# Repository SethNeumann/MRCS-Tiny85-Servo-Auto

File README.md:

# REPO NAME: MRCS-Tiny85-Servo-Auto 

## License: Creative Commons Attribution-NonCommercial-ShareAlike

Tiny85 servo switch machine controller. This version is based on load sensing to determine when the motor has completed it's travel and skipping the pots which can get bumped or drift over time.

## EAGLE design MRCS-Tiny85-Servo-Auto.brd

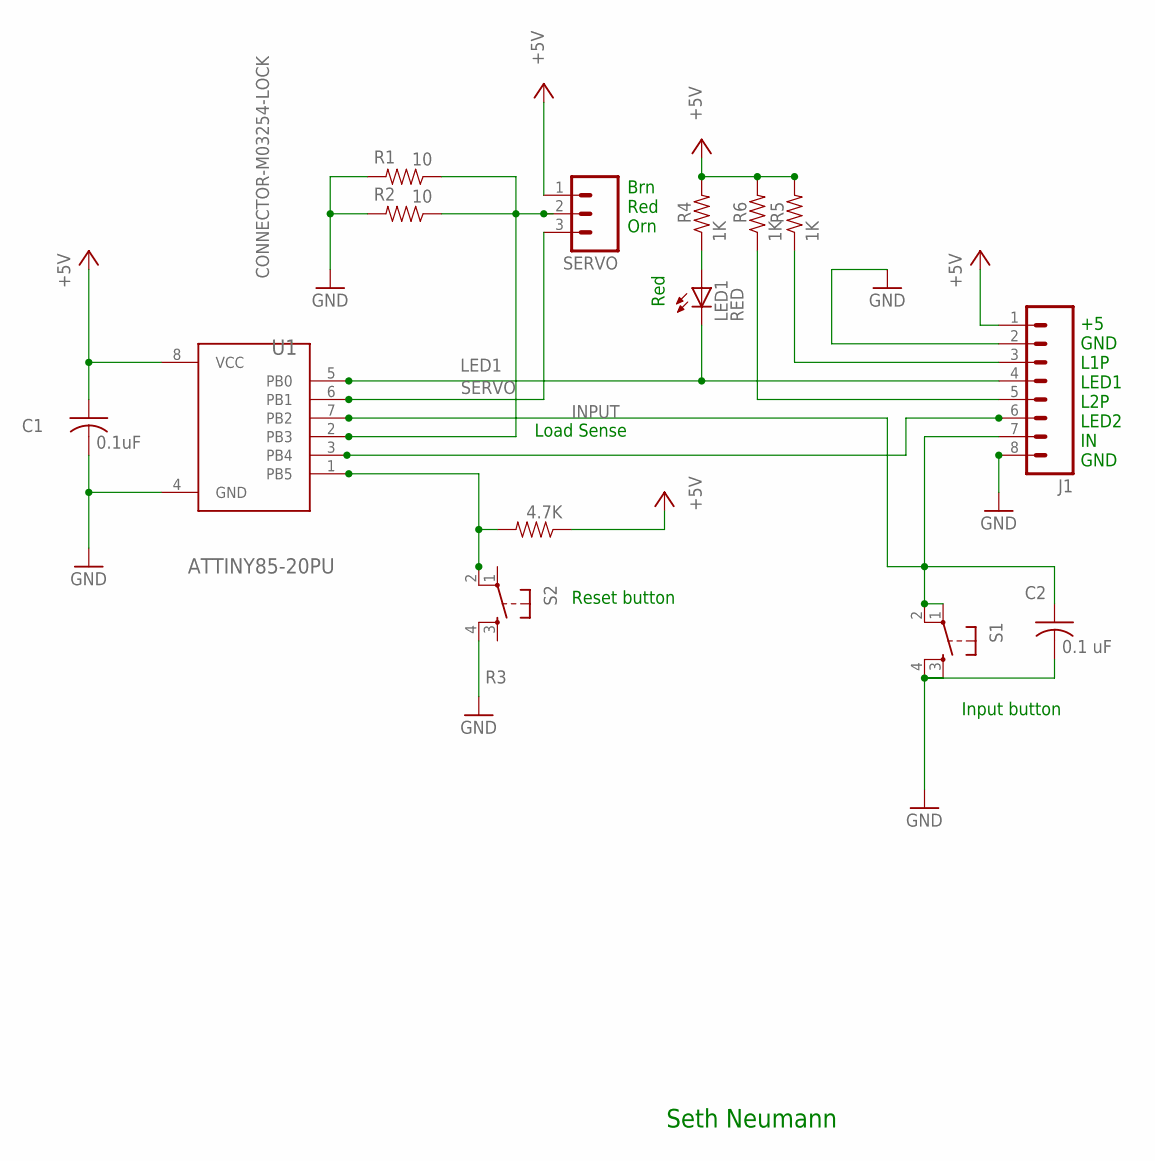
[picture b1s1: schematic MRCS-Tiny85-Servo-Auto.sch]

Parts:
C1: 0.1uF; C-PTH-0.100
C2: 0.1 uF; C-PTH-0.100
J1: CONNECTOR-M08LOCK; 1X08_LOCK
LED1: RED; LED3MM
R1, R2: 10; AXIAL-0.4-RES
R3: 4.7K; AXIAL-0.4-RES
R4, R5, R6: 1K; AXIAL-0.4-RES
S1, S2: TAC_SWITCHPTH; TACTILE-PTH
SERVO: CONNECTOR-M03254-LOCK; 3POL254
U1: ATTINY85-20PU; DIP762W46P254L927H533Q8B

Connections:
+5V: C1.1, J1.1, R3.P$1 (1), R4.P$2 (2), R5.P$2 (2), R6.P$2 (2), SERVO.1, U1.8 (VCC)
ADC3: R1.P$1 (1), R2.P$1 (1), SERVO.2, U1.2 (PB3)
GND: C1.2, C2.2, J1.2, J1.8, R1.P$2 (2), R2.P$2 (2), S1.3, S1.4, S2.4, U1.4 (GND)
INPUT: C2.1, J1.7, S1.1, S1.2, U1.7 (PB2)
LED1: J1.4, LED1.K (C), U1.5 (PB0)
LED1PWR: J1.3, R5.P$1 (1)
LED2PWR: J1.5, R6.P$1 (1)
unnamed: LED1.A, R4.P$1 (1)
unnamed: R3.P$2 (2), S2.2, U1.1 (PB5)
unnamed: J1.6, U1.3 (PB4)
SERVO: SERVO.3, U1.6 (PB1)

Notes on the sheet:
Seth Neumann
Red
Brn Red Orn
Load Sense
+5 GND L1P LED1 L2P LED2 IN GND
Reset button
Input button

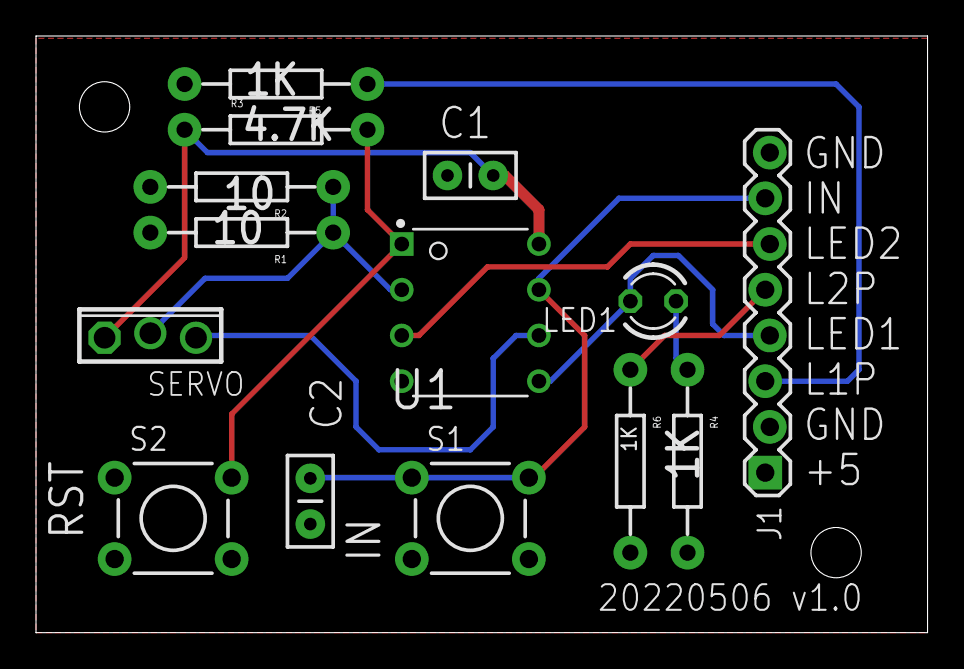
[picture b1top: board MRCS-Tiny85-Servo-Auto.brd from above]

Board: 2 copper layers, 49.5 x 33.1 mm, 17 parts (0 on the bottom side), 11 nets.

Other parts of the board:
U$1: MRCSLOGOTOP
U$2: CA-PROP65WARNING
U$3: MRCSLOGOBTM

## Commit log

2022-03-12 initial committ
2022-05-07 1st build
    Changes at Lawrence's request: added limiting resistor power for the 2nd LED and added a reset button on PB5 (pin 3).
2023-10-07 Moved one of the push buttons away from socket
    This makes it easier to remove the ATTiny for reprogramming

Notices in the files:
parts and their libraries:
SparkFun-Electromechanical: Licensing: CC v3.0 Share-Alike You are welcome to use this library for commercial purposes.
